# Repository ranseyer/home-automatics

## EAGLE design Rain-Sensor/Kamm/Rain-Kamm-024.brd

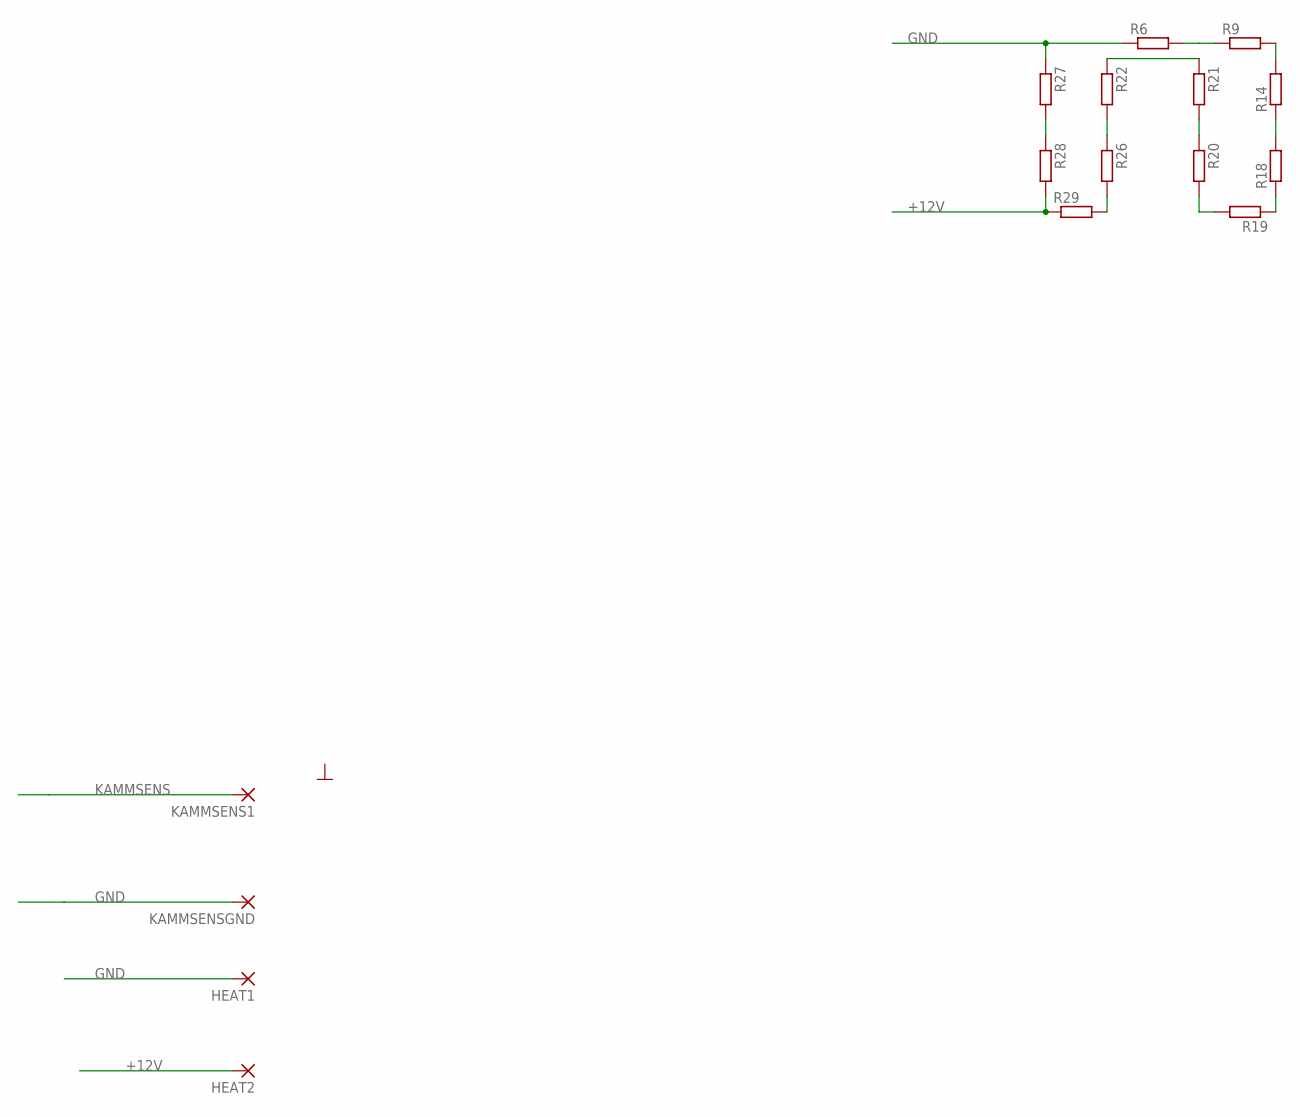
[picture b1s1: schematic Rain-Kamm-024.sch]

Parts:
HEAT1, HEAT2: WIREPADSMD5-1,8; 5-1,8
KAMMSENS1: WIREPADSMD5-1,8; 5-1,8
KAMMSENSGND: WIREPADSMD5-1,8; 5-1,8
R6, R9, R14, R18, R19, R20, R21, R22, R26, R27, R28, R29: R-EU_M1206; M1206

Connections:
+12V: HEAT2.1, R28.2, R29.1
GND: HEAT1.1, KAMMSENSGND.1, R6.1, R27.1
KAMMSENS: KAMMSENS1.1
unnamed: R20.1, R21.2
unnamed: R9.2, R14.2
unnamed: R14.1, R18.2
unnamed: R18.1, R19.1
unnamed: R19.2, R20.2
unnamed: R6.2, R9.1
unnamed: R21.1, R22.1
unnamed: R22.2, R26.1
unnamed: R26.2, R29.2
unnamed: R27.2, R28.1

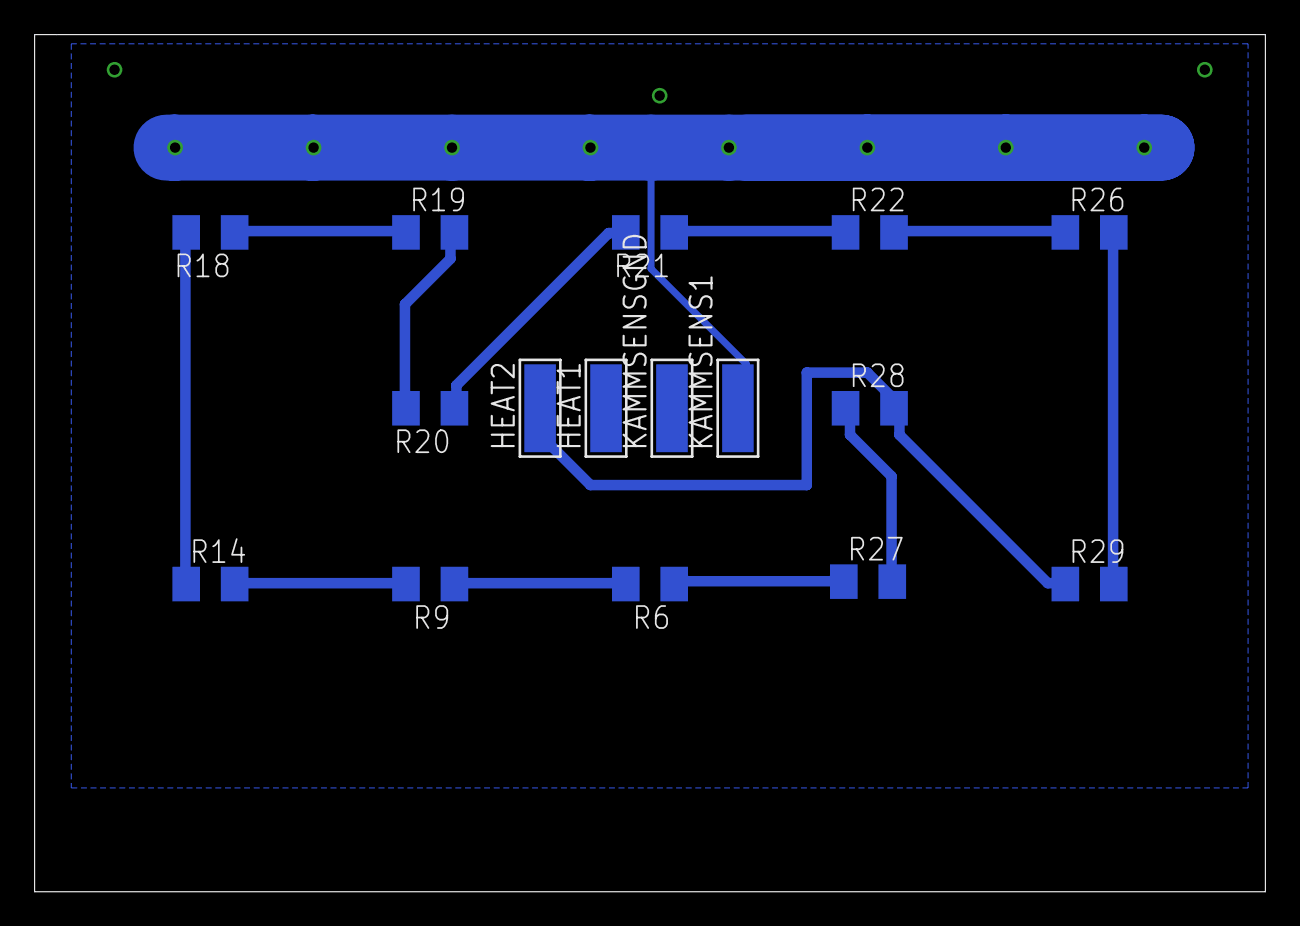
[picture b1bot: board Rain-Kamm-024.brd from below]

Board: 2 copper layers, 71.1 x 49.5 mm, 16 parts (16 on the bottom side), 12 nets.

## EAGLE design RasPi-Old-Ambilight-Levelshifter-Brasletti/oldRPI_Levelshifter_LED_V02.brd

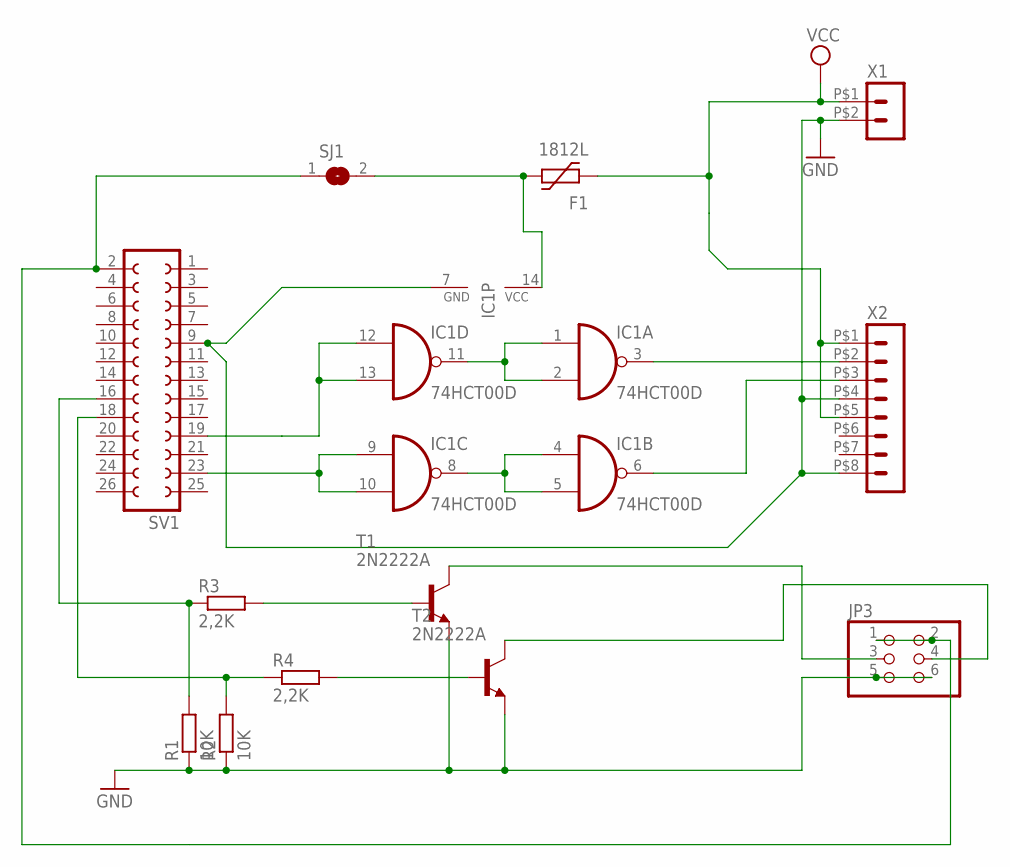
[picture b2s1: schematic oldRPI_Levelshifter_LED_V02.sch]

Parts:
F1: 1812L
IC1: 74HCT00D; SO14
JP3: PINHD-2X3/90; 2X03/90
R1, R2: 10K; R1206
R3, R4: 2,2K; R1206
SJ1: SJ
SV1: FE13-2
T1, T2: 2N2222A; SOT23-EBC
X1: HEADER_POS2_43045-0200; 43045-0200
X2: HEADER_POS8_43045-0800; 43045-0800

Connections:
5V_RPI: JP3.1, JP3.2, SJ1.1, SV1.2
GND: IC1.7 (GND), JP3.5, JP3.6, R1.1, R2.1, SV1.9, T1.E, T2.E, X1.P$2 (2), X2.P$4 (4), X2.P$8 (8)
unnamed: IC1.1 (I0), IC1.2 (I1), IC1.11 (O)
unnamed: F1.P$2 (2), IC1.14 (VCC), SJ1.2
unnamed: IC1.4 (I0), IC1.5 (I1), IC1.8 (O)
unnamed: IC1.3 (O), X2.P$2 (2)
unnamed: IC1.12 (I0), IC1.13 (I1), SV1.19
unnamed: IC1.9 (I0), IC1.10 (I1), SV1.23
unnamed: IC1.6 (O), X2.P$3 (3)
unnamed: R3.2, T1.B
unnamed: R4.2, T2.B
unnamed: JP3.3, T1.C
unnamed: JP3.4, T2.C
unnamed: R2.2, R4.1, SV1.18
unnamed: R1.2, R3.1, SV1.16
VCC: F1.P$1 (1), X1.P$1 (1), X2.P$1 (1), X2.P$5 (5)

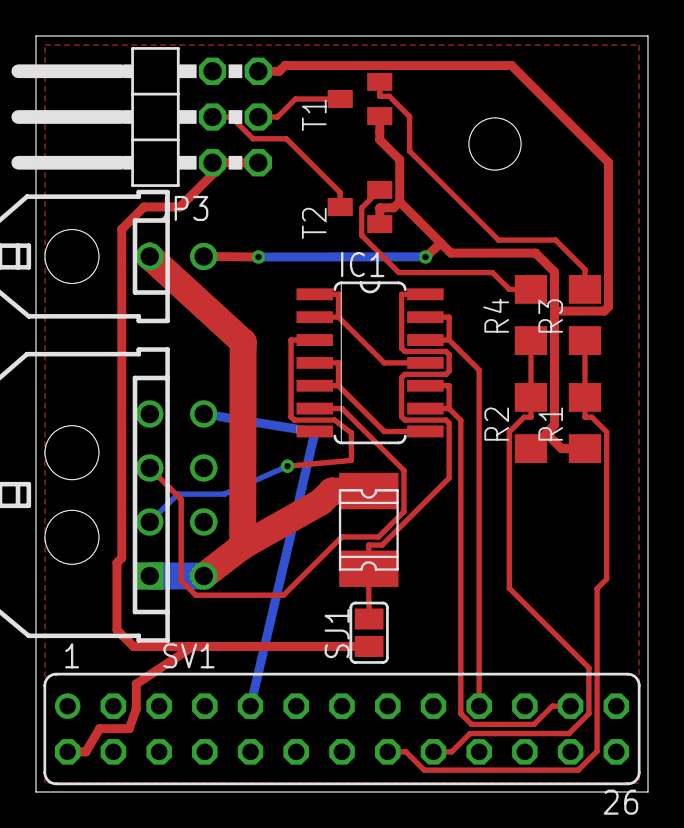
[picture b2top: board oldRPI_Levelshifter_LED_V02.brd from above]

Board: 2 copper layers, 34.0 x 42.0 mm, 13 parts (0 on the bottom side), 16 nets.

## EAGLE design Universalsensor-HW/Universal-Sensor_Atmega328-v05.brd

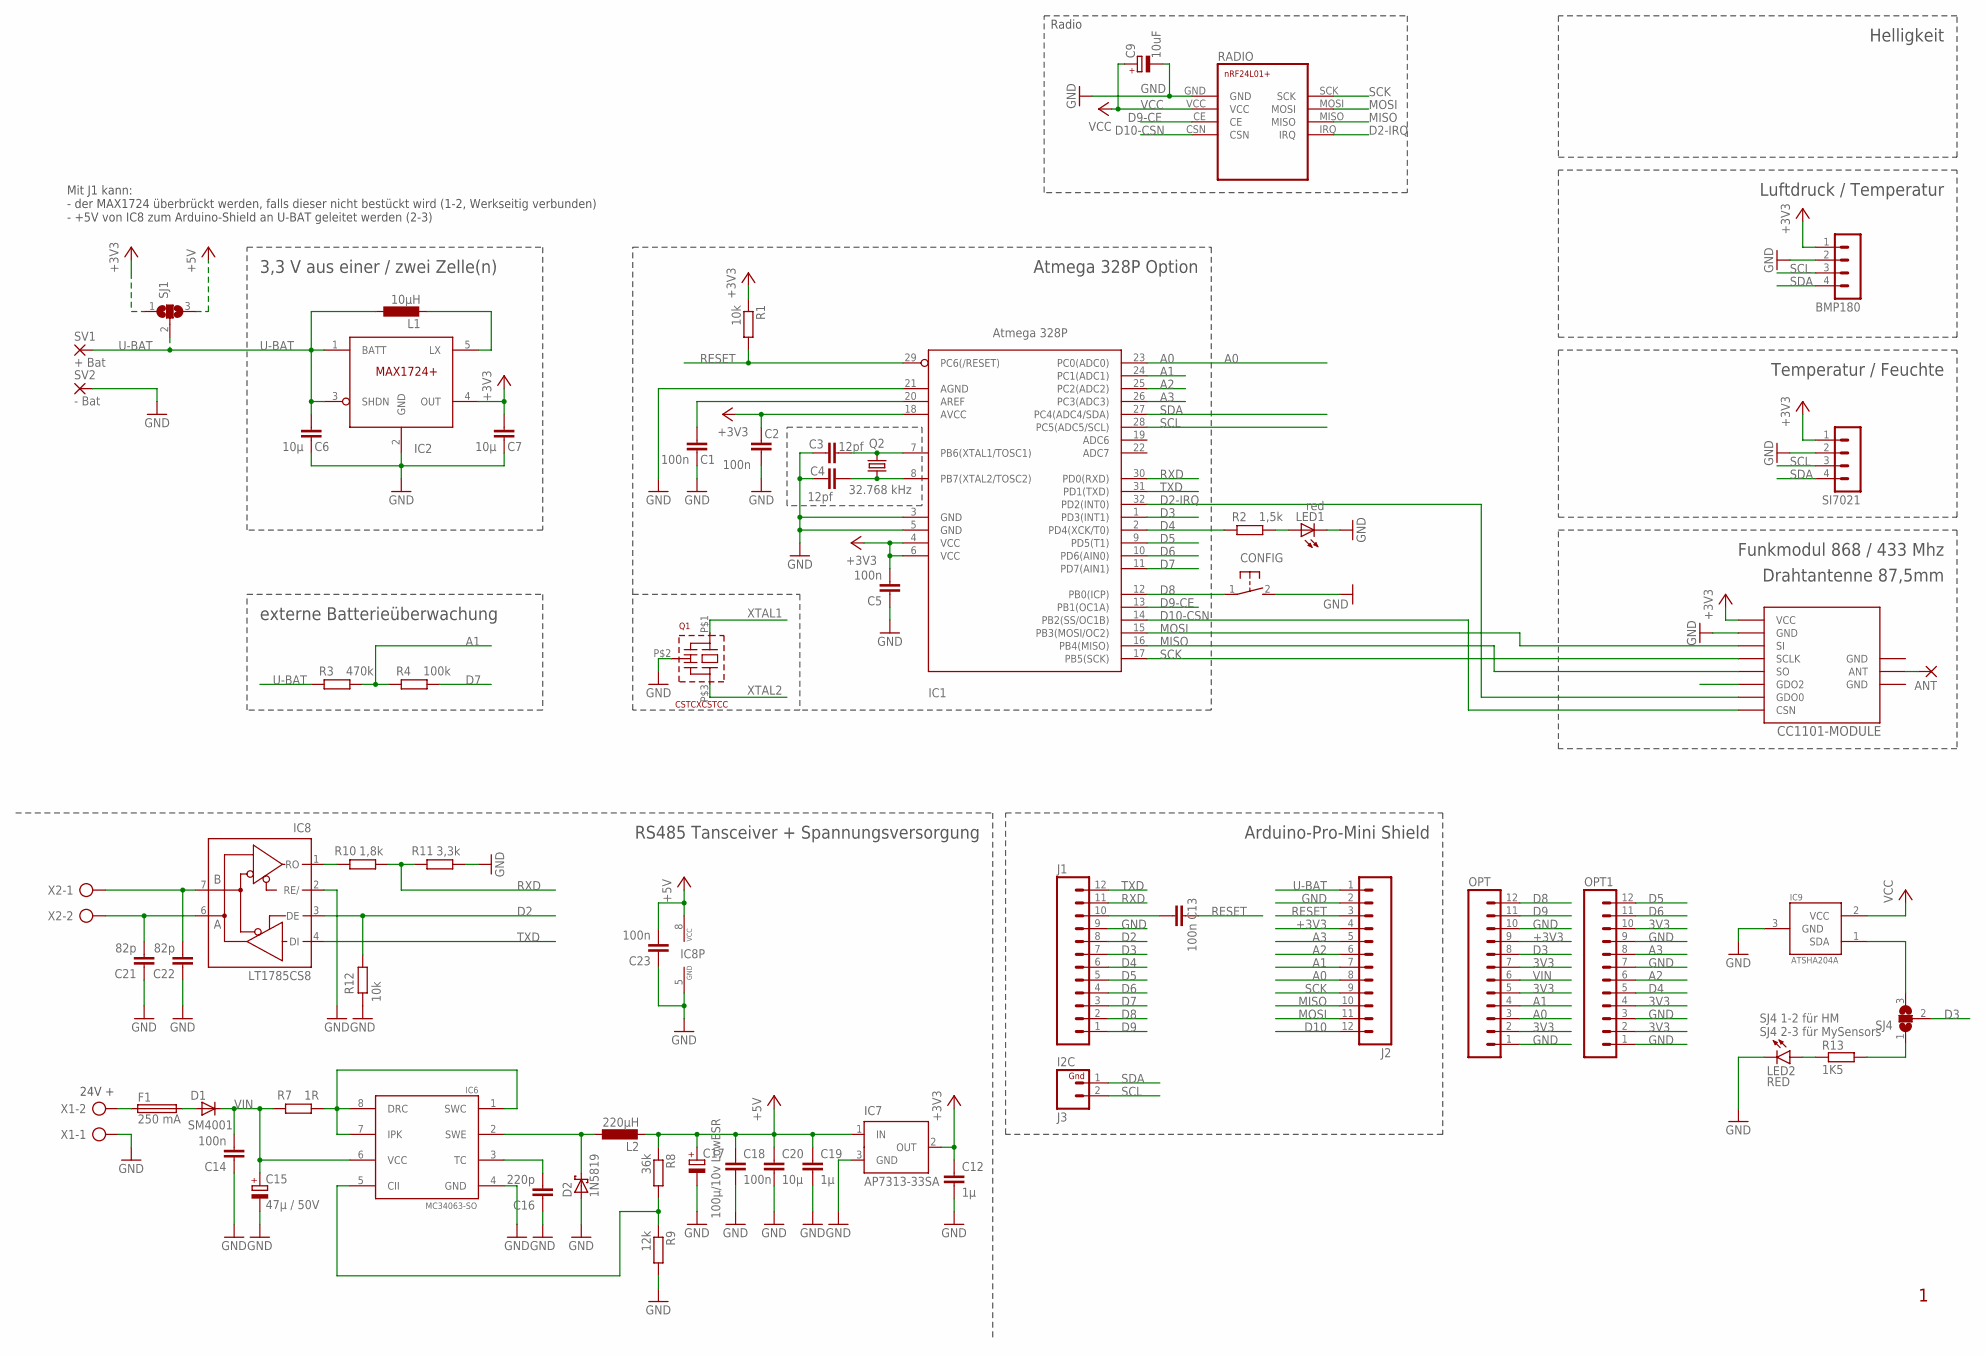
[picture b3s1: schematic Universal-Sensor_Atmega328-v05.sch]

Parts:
ANT: 1,6/0,8
BMP180: MA04-1
C1, C2, C5, C13, C18, C23: 100n; C0805
C3, C4: 12pf; C0805
C6, C7, C20: 10µ; C1206
C9: 10uF; E2,5-6E
C12, C19: 1µ; C0805
C14: 100n; C1206
C15: 47µ / 50V; E2,5-7
C16: 220p; C0805
C17: 100µ/10v LowESR; SMC_D
C21, C22: 82p; C0805
CC1101-MODULE: CC1101_WIRELES_MODULE
CONFIG: DTSM-3
D1: SM4001; MELF-MLL41
D2: 1N5819; SMB
F1: 250 mA; SMD-6,1X2,6
IC1: Atmega 328P; TQFP32-08
IC2: MAX1724; SOT23-5L
IC6: MC34063-SO; SO8
IC7: AP7313-33SA; SOT23
IC8: LT1785CS8; SO08
IC9: ATSHA204A; SOT23-3
J1, J2: M12PTH; 1X12
J3: I2C; 1X02
L1: 10µH; L4532P
L2: 220µH; L5650M
LED1: red; CHIP-LED0805
LED2: RED; LED-1206
OPT, OPT1: M12PTH; 1X12
Q1: CSTCXCSTCC; CSTCC
Q2: 32.768 kHz; TC38H
R1, R12: 10k; M0805
R2: 1,5k; M0805
R3: 470k; M0805
R4: 100k; M0805
R7: 1R; R0805
R8: 36k; R0805
R9: 12k; R0805
R10: 1,8k; R0805
R11: 3,3k; R0805
R13: 1K5; R0805_SMALL_GAP
RADIO: NRF24L01+
SI7021: MA04-1
SJ1, SJ4: SJ2W; SJ_2
SV1: + Bat; 1,6/0,9
SV2: - Bat; 1,6/0,9
X1, X2: AK550/2

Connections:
3V3: OPT.2, OPT.5, OPT.7, OPT1.2, OPT1.4, OPT1.10
+3V3: BMP180.1, C2.2, C5.2, C7.2, C12.1, CC1101-MODULE.VCC, IC1.4 (VCC), IC1.6 (VCC), IC1.18 (AVCC), IC2.4 (OUT), IC7.2 (OUT), J2.4, OPT.9, R1.1, SI7021.1, SJ1.1
+5V: C17.+, C18.1, C19.1, C20.1, C23.2, IC7.1 (IN), IC8.8 (VCC), L2.2, R8.1, SJ1.3
A: C21.2, IC8.6 (A), X2.2
A0: IC1.23 (PC0(ADC0)), J2.8, OPT.3
A1: IC1.24 (PC1(ADC1)), J2.7, OPT.4, R3.2, R4.1
A2: IC1.25 (PC2(ADC2)), J2.6, OPT1.6
A3: IC1.26 (PC3(ADC3)), J2.5, OPT1.8
ATSHA: IC9.1 (SDA), SJ4.3
B: C22.2, IC8.7 (B), X2.1
D2: IC8.3 (DE), J1.8, R12.2
D2-IRQ: CC1101-MODULE.GDO0, IC1.32 (PD2(INT0)), RADIO.IRQ
D3: IC1.1 (PD3(INT1)), J1.7, OPT.8, SJ4.2
D4: IC1.2 (PD4(XCK/T0)), J1.6, OPT1.5, R2.1
D5: IC1.9 (PD5(T1)), J1.5, OPT1.12
D6: IC1.10 (PD6(AIN0)), J1.4, OPT1.11
D7: IC1.11 (PD7(AIN1)), J1.3, R4.2
D8: CONFIG.1, IC1.12 (PB0(ICP)), J1.2, OPT.12
D9: J1.1, OPT.11
D9-CE: IC1.13 (PB1(OC1A)), RADIO.CE
D10: J2.12
D10-CSN: CC1101-MODULE.CSN, IC1.14 (PB2(SS/OC1B)), RADIO.CSN
GND: BMP180.2, C1.1, C2.1, C3.2, C4.2, C5.1, C6.1, C7.1, C9.-, C12.2, C14.1, C15.-, C16.1, C17.-, C18.2, C19.2, C20.2, C21.1, C22.1, C23.1, CC1101-MODULE.GND@1 (GND), CC1101-MODULE.GND@2 (GND), CC1101-MODULE.GND@3 (GND), CONFIG.2, D2.A, IC1.3 (GND), IC1.5 (GND), IC1.21 (AGND), IC2.2 (GND), IC6.4 (GND), IC7.3 (GND), IC8.2 (RE/), IC8.5 (GND), IC9.3 (GND), J1.9, J2.2, LED1.C, LED2.C, OPT.1, OPT.10, OPT1.1, OPT1.3, OPT1.7, OPT1.9, Q1.P$2 (GND), R9.2, R11.1, R12.1, RADIO.GND, SI7021.2, SV2.1, X1.1
LED: R13.2, SJ4.1
MISO: CC1101-MODULE.SO, IC1.16 (PB4(MISO)), J2.10, RADIO.MISO
MOSI: CC1101-MODULE.SI, IC1.15 (PB3(MOSI/OC2)), J2.11, RADIO.MOSI
unnamed: C13.2, J1.10
unnamed: IC2.5 (LX), L1.2
unnamed: LED1.A, R2.2
unnamed: ANT.1, CC1101-MODULE.ANT
unnamed: LED2.A, R13.1
unnamed: F1.1, X1.2
unnamed: IC8.1 (RO), R10.2
unnamed: C1.2, IC1.20 (AREF)
unnamed: D1.A, F1.2
unnamed: IC6.1 (SWC), IC6.7 (IPK), IC6.8 (DRC), R7.1
unnamed: IC6.5 (CII), R8.2, R9.1
unnamed: C16.2, IC6.3 (TC)
unnamed: D2.C, IC6.2 (SWE), L2.1
RESET: C13.1, IC1.29 (PC6(/RESET)), J2.3, R1.2
RXD: IC1.30 (PD0(RXD)), J1.11, R10.1, R11.2
SCK: CC1101-MODULE.SCLK, IC1.17 (PB5(SCK)), J2.9, RADIO.SCK
SCL: BMP180.3, IC1.28 (PC5(ADC5/SCL)), J3.2, SI7021.3
SDA: BMP180.4, IC1.27 (PC4(ADC4/SDA)), J3.1, SI7021.4
TXD: IC1.31 (PD1(TXD)), IC8.4 (DI), J1.12
U-BAT: C6.2, IC2.1 (BATT), IC2.3 (SHDN), J2.1, L1.1, R3.1, SJ1.2, SV1.1
VCC: C9.+, IC9.2 (VCC), RADIO.VCC
VIN: C14.2, C15.+, D1.C, IC6.6 (VCC), OPT.6, R7.2
XTAL1: C3.1, IC1.7 (PB6(XTAL1/TOSC1)), Q1.P$1 (1), Q2.2
XTAL2: C4.1, IC1.8 (PB7(XTAL2/TOSC2)), Q1.P$3 (3), Q2.1

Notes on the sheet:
Mit J1 kann: - der MAX1724 überbrückt werden, falls dieser nicht bestückt wird (1-2, Werkseitig verbunden) - +5V von IC8 zum Arduino-Shield an U-BAT geleitet werden (2-3)
24V +
RS485 Tansceiver + Spannungsversorgung
3,3 V aus einer / zwei Zelle(n)
externe Batterieüberwachung
Arduino-Pro-Mini Shield
Atmega 328P Option
Helligkeit
Luftdruck / Temperatur
Temperatur / Feuchte
Funkmodul 868 / 433 Mhz
Drahtantenne 87,5mm
IC2
SJ4 1-2 für HM SJ4 2-3 für MySensors
Radio

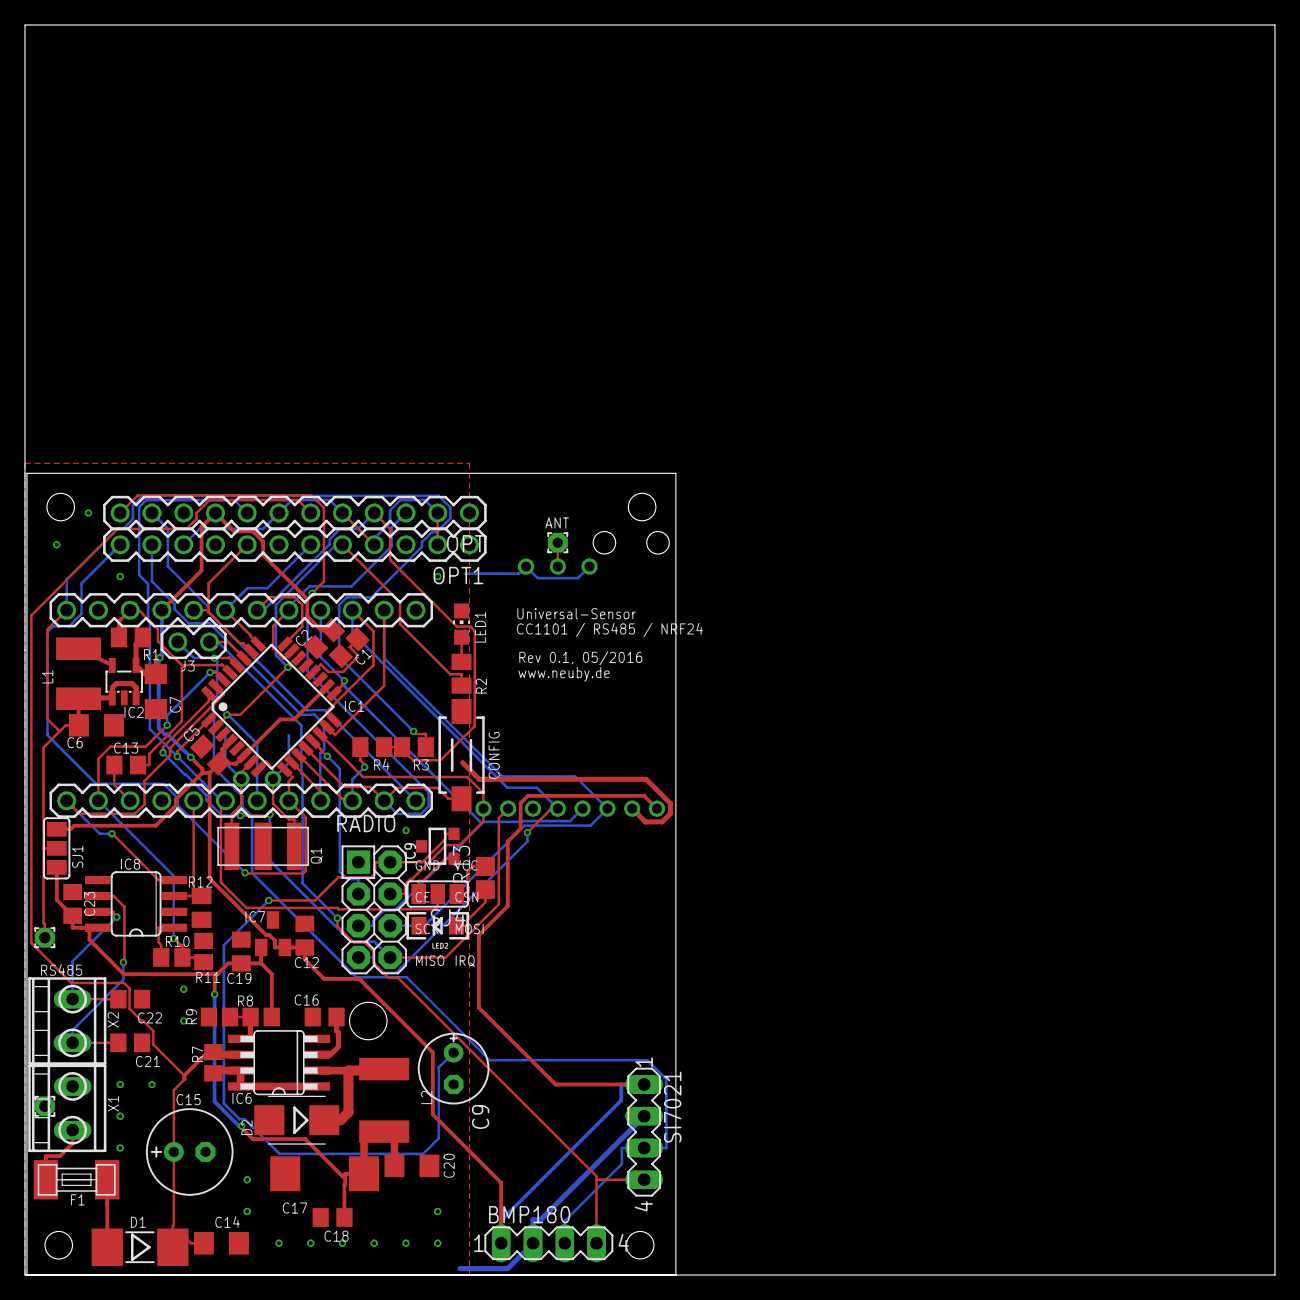
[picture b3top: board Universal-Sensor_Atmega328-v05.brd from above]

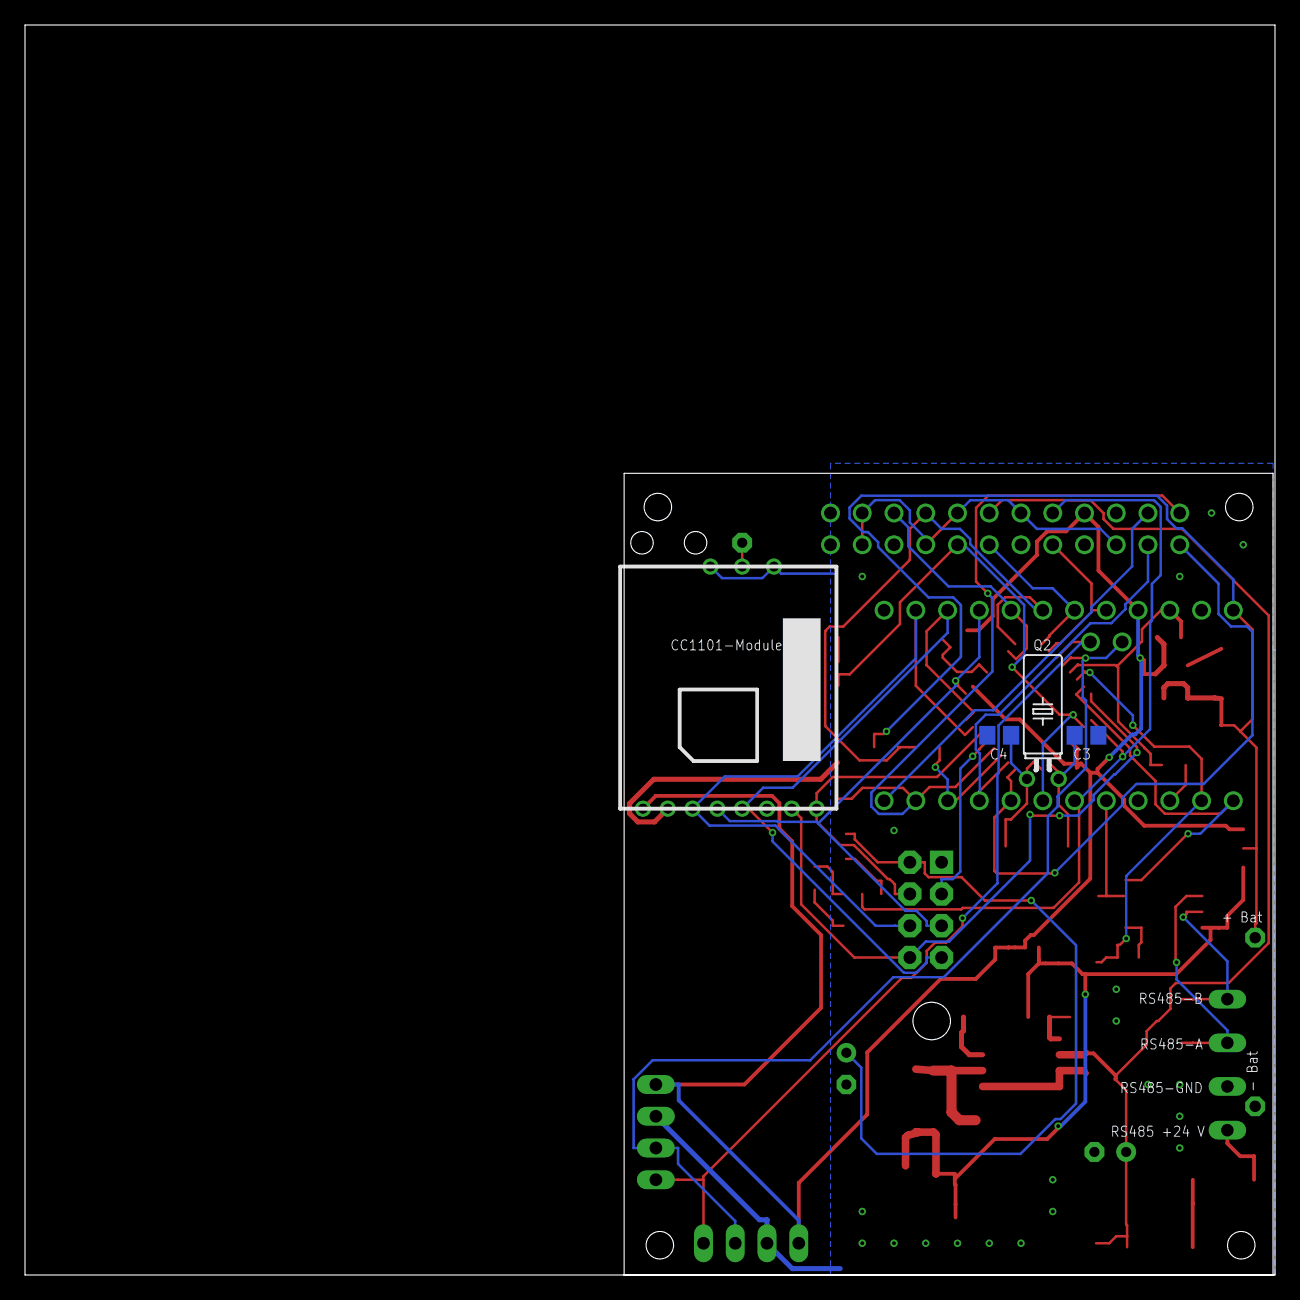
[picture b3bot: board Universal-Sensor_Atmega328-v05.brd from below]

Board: 2 copper layers, 100.0 x 100.0 mm, 63 parts (4 on the bottom side), 49 nets.

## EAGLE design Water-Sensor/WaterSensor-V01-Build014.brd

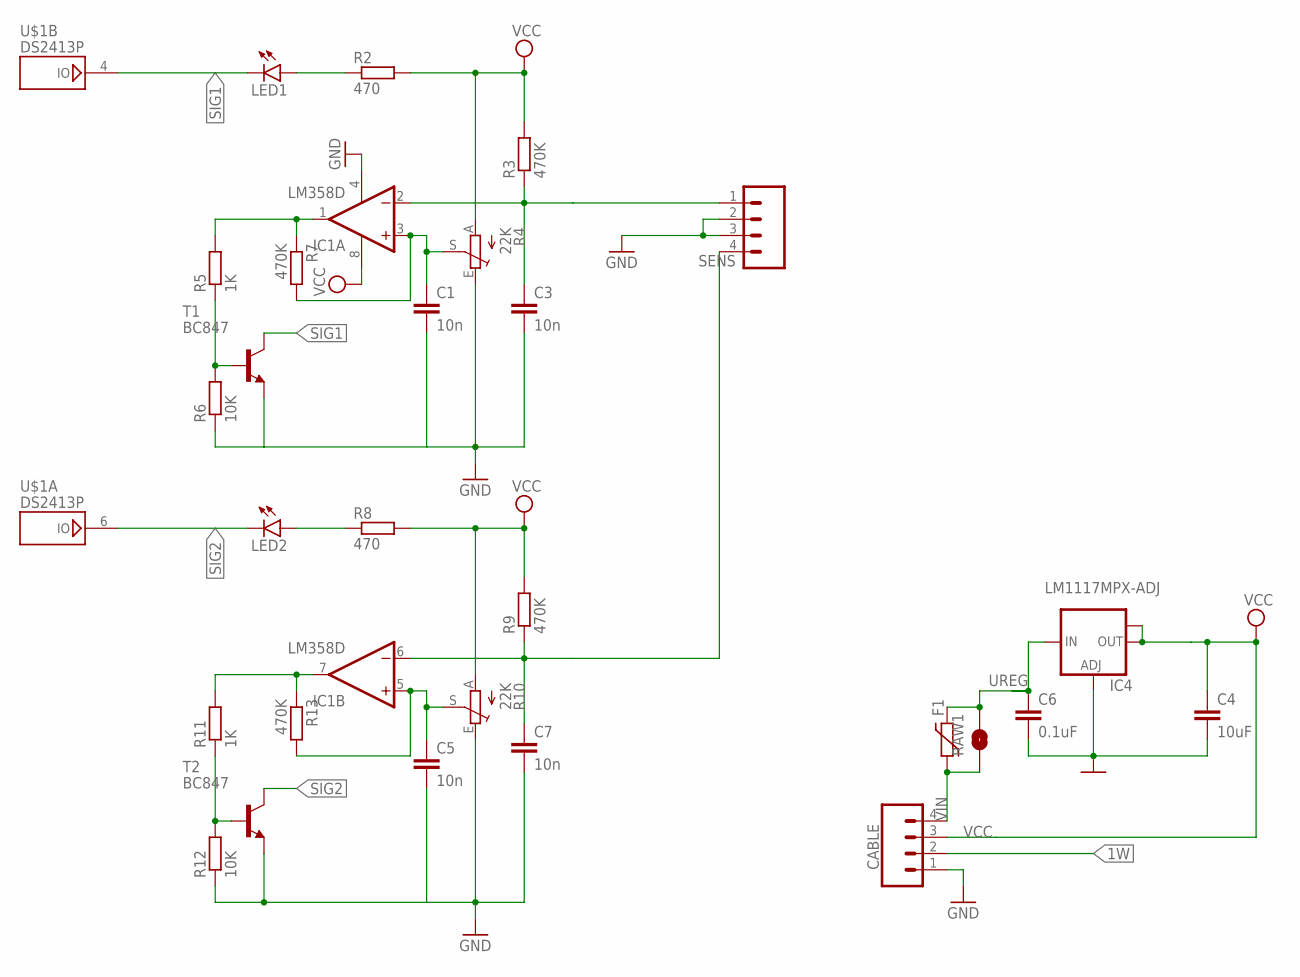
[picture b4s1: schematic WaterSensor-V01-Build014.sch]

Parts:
C1, C3, C5, C7: 10n; C0805K
C4: 10uF; C1210
C6: 0.1uF; C1206
CABLE: CONN_04LONGPADS; 1X04_LONGPADS
F1: 1812L
IC1: LM358D; SO08
IC4: LM1117MPX-ADJ; SOT223
LED1, LED2: LEDCHIP-LED0805; CHIP-LED0805
R2, R8: 470; R0805W
R3, R7, R9, R13: 470K; R0805W
R4, R10: 22K; CA6V
R5, R11: 1K; R0805W
R6, R12: 10K; R0805W
RAW1: JUMPER-SMT_2_NO_SILK; SMT-JUMPER_2_NO_SILK
SENS: CONN_04LONGPADS; 1X04_LONGPADS
T1, T2: BC847; SOT23
U$1: DS2413P; TSOC6

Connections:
1W: CABLE.2, U$1.2 (1W)
GND: C1.2, C3.2, C4.2, C5.2, C6.2, C7.2, CABLE.1, IC1.4 (V-), IC4.1 (ADJ), R4.E, R6.1, R10.E, R12.1, SENS.2, SENS.3, T1.2 (E), T2.2 (E), U$1.1 (GND), U$1.5 (GND)
unnamed: LED1.A, R2.1
unnamed: C3.1, IC1.2 (-IN), R3.1, SENS.1
unnamed: IC1.1 (OUT), R5.2, R7.1
unnamed: C1.1, IC1.3 (+IN), R4.S, R7.2
unnamed: LED2.A, R8.1
unnamed: R5.1, R6.2, T1.1 (B)
unnamed: C7.1, IC1.6 (-IN), R9.1, SENS.4
unnamed: IC1.7 (OUT), R11.2, R13.1
unnamed: C5.1, IC1.5 (+IN), R10.S, R13.2
unnamed: R11.1, R12.2, T2.1 (B)
SIG1: LED1.C, T1.3 (C), U$1.4 (IO)
SIG2: LED2.C, T2.3 (C), U$1.6 (IO)
UREG: C6.1, F1.P$1 (1), IC4.3 (IN), RAW1.2
VCC: C4.1, CABLE.3, IC1.8 (V+), IC4.2 (OUT), IC4.TAB (OUT1), R2.2, R3.2, R4.A, R8.2, R9.2, R10.A
VIN: CABLE.4, F1.P$2 (2), RAW1.1

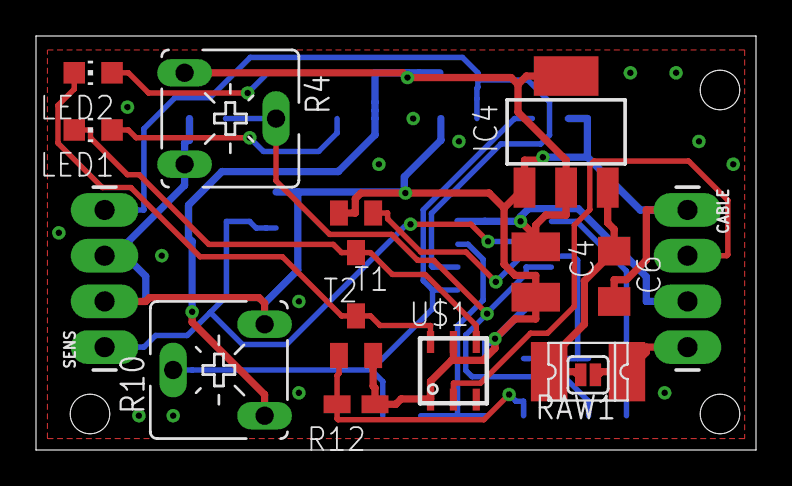
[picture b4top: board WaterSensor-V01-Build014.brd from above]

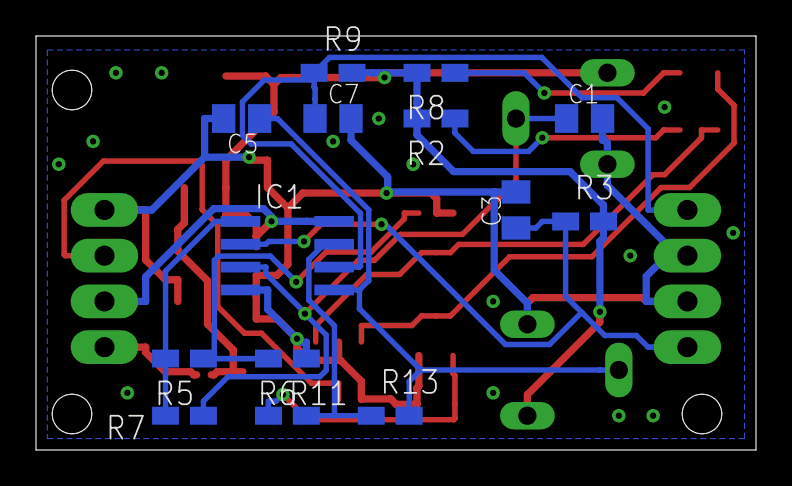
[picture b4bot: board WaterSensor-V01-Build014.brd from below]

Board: 2 copper layers, 40.0 x 23.0 mm, 29 parts (14 on the bottom side), 17 nets.

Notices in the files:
parts and their libraries:
SparkFun-LED: Licensing: Creative Commons ShareAlike 4.0 International - https://creativecommons.org/licenses/by-sa/4.0
